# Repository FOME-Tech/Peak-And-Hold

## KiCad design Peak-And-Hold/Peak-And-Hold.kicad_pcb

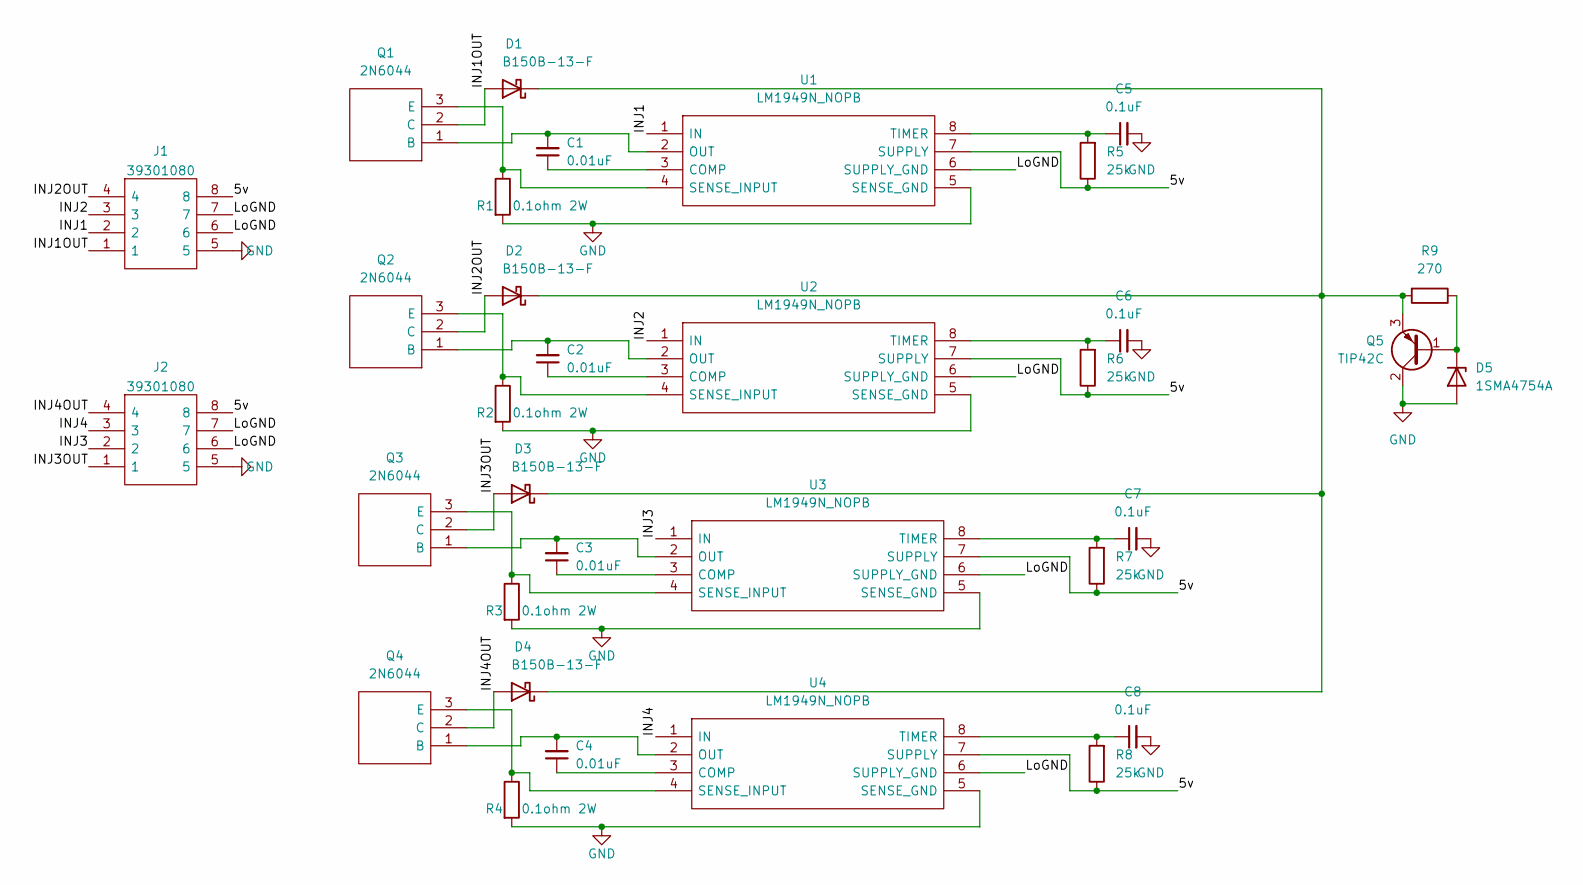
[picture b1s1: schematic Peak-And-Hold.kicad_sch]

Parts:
C1, C2, C3, C4: 0.01uF; C_1206_3216Metric; LCSC C77494
C5, C6, C7, C8: 0.1uF; C_1206_3216Metric; LCSC C77494
D1, D2, D3, D4: B150B-13-F; D_SMB; LCSC C134432
D5: 1SMA4754A; D_SMA; LCSC C2903856
J1, J2: 39301080; Molex_Mini-Fit_Jr_5569-08A2_2x04_P4.20mm_Horizontal; Manufacturer_Part_Number 39301080
Q1, Q2, Q3, Q4: 2N6044; TO-220-3_Vertical; Manufacturer_Part_Number 2N6044; Mouser Part Number 610-2N6044
Q5: TIP42C; TO-220-3_Vertical
R1, R2, R3, R4: 0.1ohm 2W; R_Axial_DIN0414_L11.9mm_D4.5mm_P15.24mm_Horizontal
R5, R6, R7, R8: 25k; R_0805_2012Metric; LCSC C2907326
R9: 270; R_0805_2012Metric; LCSC C2907326
U1, U2, U3, U4: LM1949N_NOPB; DIP-8_W7.62mm; Manufacturer_Part_Number LM1949N/NOPB; Mouser Part Number 926-LM1949N/NOPB

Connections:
/5v: J1.8, J2.8, R5.1, R6.1, R7.1, R8.1, U1.7 (SUPPLY), U2.7 (SUPPLY), U3.7 (SUPPLY), U4.7 (SUPPLY)
/INJ1: J1.2, U1.1 (IN)
/INJ1OUT: D1.2 (A), J1.1, Q1.2 (C)
/INJ2: J1.3, U2.1 (IN)
/INJ2OUT: D2.2 (A), J1.4, Q2.2 (C)
/INJ3: J2.2, U3.1 (IN)
/INJ3OUT: D3.2 (A), J2.1, Q3.2 (C)
/INJ4: J2.3, U4.1 (IN)
/INJ4OUT: D4.2 (A), J2.4, Q4.2 (C)
/LoGND: J1.6, J1.7, J2.6, J2.7, U1.6 (SUPPLY_GND), U2.6 (SUPPLY_GND), U3.6 (SUPPLY_GND), U4.6 (SUPPLY_GND)
GND: C5.2, C6.2, C7.2, C8.2, D5.2 (A), J1.5, J2.5, Q5.2 (C), R1.2, R2.2, R3.2, R4.2, U1.5 (SENSE_GND), U2.5 (SENSE_GND), U3.5 (SENSE_GND), U4.5 (SENSE_GND)
unnamed: C1.1, U1.3 (COMP)
unnamed: C1.2, Q1.1 (B), U1.2 (OUT)
unnamed: C2.1, U2.3 (COMP)
unnamed: C2.2, Q2.1 (B), U2.2 (OUT)
unnamed: C3.1, U3.3 (COMP)
unnamed: C3.2, Q3.1 (B), U3.2 (OUT)
unnamed: C4.1, U4.3 (COMP)
unnamed: C4.2, Q4.1 (B), U4.2 (OUT)
unnamed: C5.1, R5.2, U1.8 (TIMER)
unnamed: C6.1, R6.2, U2.8 (TIMER)
unnamed: C7.1, R7.2, U3.8 (TIMER)
unnamed: C8.1, R8.2, U4.8 (TIMER)
unnamed: D1.1 (K), D2.1 (K), D3.1 (K), D4.1 (K), Q5.3 (E), R9.2
unnamed: D5.1 (K), Q5.1 (B), R9.1
unnamed: Q1.3 (E), R1.1, U1.4 (SENSE_INPUT)
unnamed: Q2.3 (E), R2.1, U2.4 (SENSE_INPUT)
unnamed: Q3.3 (E), R3.1, U3.4 (SENSE_INPUT)
unnamed: Q4.3 (E), R4.1, U4.4 (SENSE_INPUT)

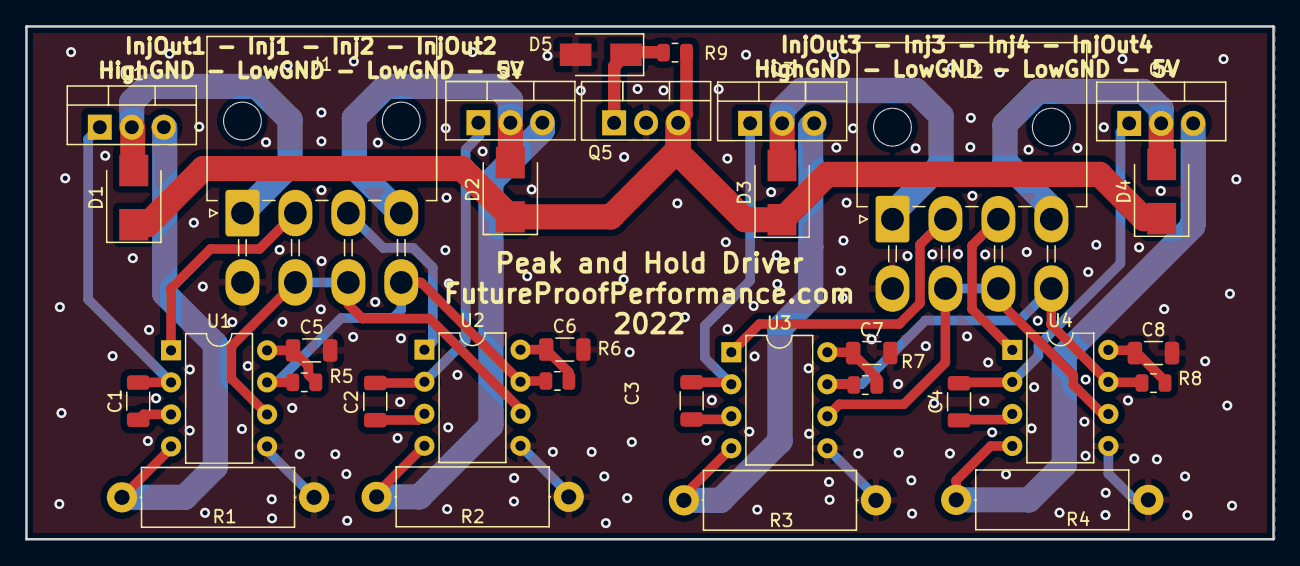
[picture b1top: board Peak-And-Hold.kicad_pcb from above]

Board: 2 copper layers, 98.9 x 40.7 mm, 33 parts (0 on the bottom side), 29 nets.

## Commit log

2022-10-31 Basically designed in one shot
2022-11-01 added plugs
2022-11-02 finished off
2022-11-02 Fabrication Ready
